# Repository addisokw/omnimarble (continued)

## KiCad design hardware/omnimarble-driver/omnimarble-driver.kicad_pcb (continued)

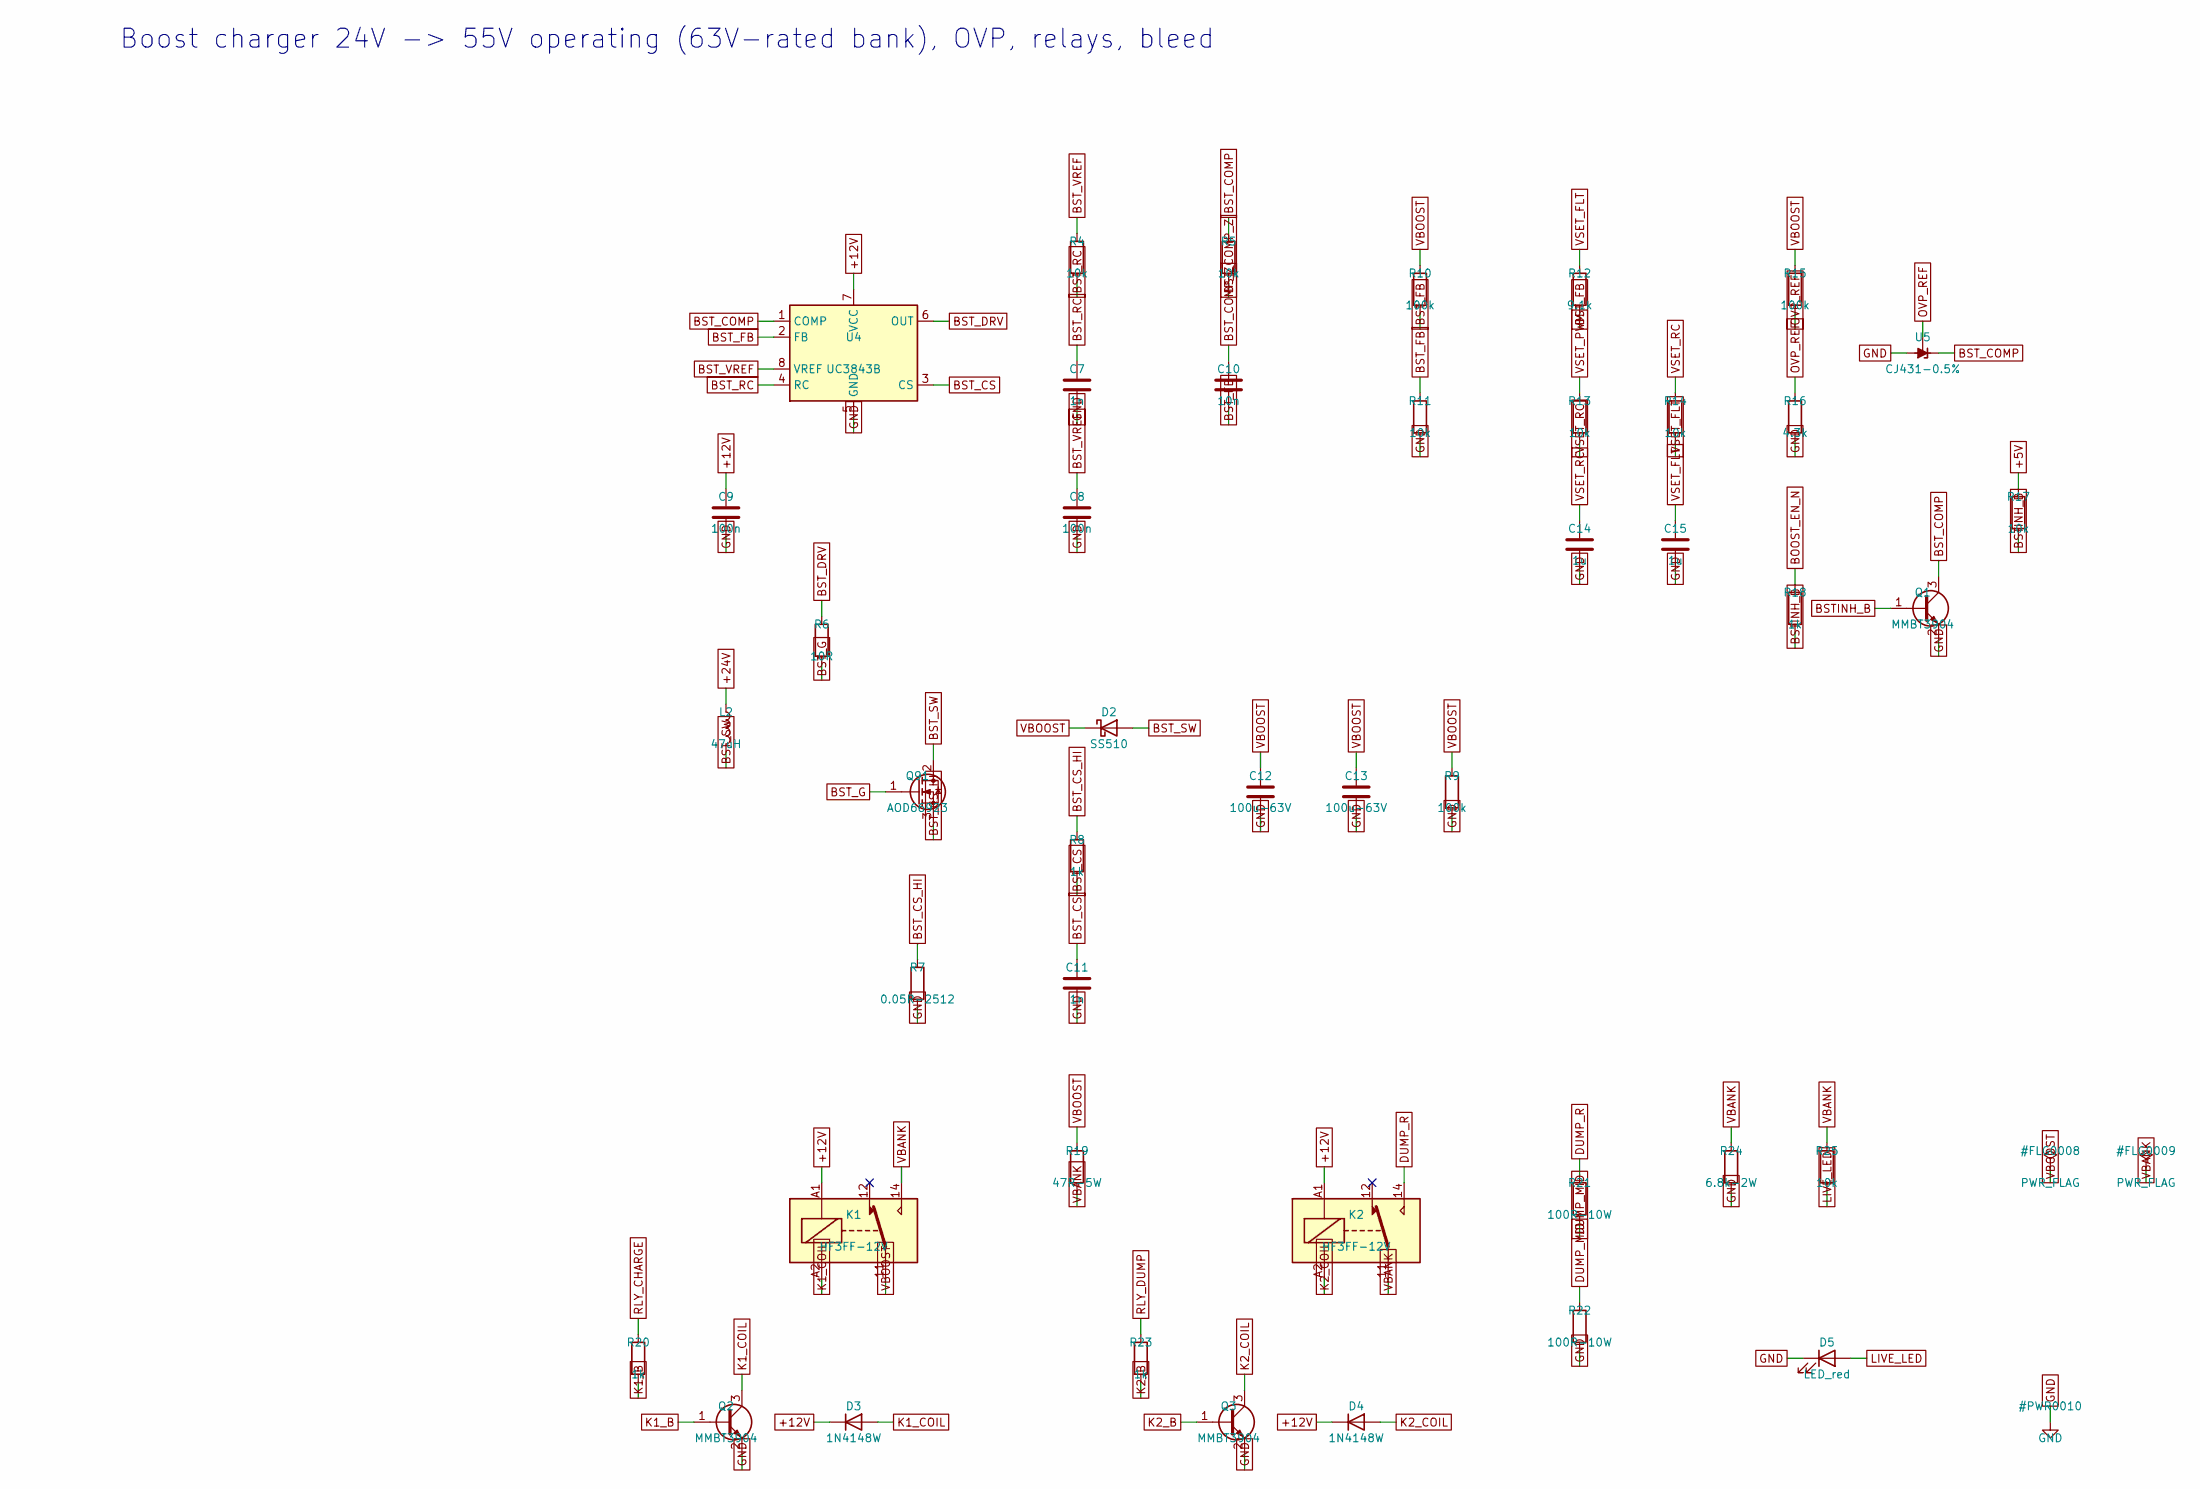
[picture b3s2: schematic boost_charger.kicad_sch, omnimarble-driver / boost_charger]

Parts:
C7, C11: 1n; C_0603_1608Metric; LCSC C1588
C8, C9: 100n; C_0603_1608Metric; LCSC C14663
C10: 10n; C_0603_1608Metric; LCSC C57112
C12, C13: 100u-63V; CP_Elec_10x10.5; LCSC C28241
C14, C15: 1u; C_0603_1608Metric; LCSC C15849
D2: SS510; D_SMA; LCSC C65010
D3, D4: 1N4148W; D_SOD-123; LCSC C81598
D5: LED_red; LED_0603_1608Metric; LCSC C2286
K1, K2: HF3FF-12V; Relay_HF3FF_T73; LCSC C399561
L2: 47uH; L_12x12mm_H8mm; LCSC C497913
Q1, Q2, Q3: MMBT3904; SOT-23; LCSC C20526
Q91: AOD66923; TO-252-2; LCSC C485687
R4, R5, R11, R13, R14, R17, R25: 10k; R_0603_1608Metric; LCSC C25804
R6: 10R; R_0603_1608Metric; LCSC C22859
R7: 0.05R-2512; R_2512_6332Metric; LCSC C2994645
R8, R18, R20, R23: 1k; R_0603_1608Metric; LCSC C21190
R9, R10, R15: 100k; R_0603_1608Metric; LCSC C25803
R12: 9.1k; R_0603_1608Metric; LCSC C23260
R16: 4.3k; R_0603_1608Metric; LCSC C23159
R19: 47R-5W; R_Box_L26.0mm_W5.0mm_P20.00mm; LCSC C5807995
R21, R22: 100R-10W; R_Radial_Power_L11.0mm_W7.0mm_P5.00mm; LCSC C216413
R24: 6.8k-2W; R_2512_6332Metric; LCSC ORDER-REVIEW
U4: UC3843B; SOIC-8_3.9x4.9mm_P1.27mm; LCSC C16414
U5: CJ431-0.5%; SOT-23; LCSC C3113

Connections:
+5V: R17.1; also elsewhere on the board
+12V: C9.1, D3.1 (K), D4.1 (K), K1.A1, K2.A1, U4.7 (VCC); also elsewhere on the board
+24V: L2.1; also elsewhere on the board
BOOST_EN_N: R18.1; also elsewhere on the board
BSTINH_B: Q1.1 (B), R17.2, R18.2
BST_COMP: Q1.3 (C), R5.1, U4.1 (COMP), U5.1 (K)
BST_COMP_Z: C10.1, R5.2
BST_CS: C11.1, R8.2, U4.3 (CS)
BST_CS_HI: Q91.3 (S), R7.1, R8.1
BST_DRV: R6.1, U4.6 (OUT)
BST_FB: C10.2, R10.2, R11.1, R12.2, U4.2 (FB)
BST_G: Q91.1 (G), R6.2
BST_RC: C7.1, R4.2, U4.4 (RC)
BST_SW: D2.2 (A), L2.2, Q91.2 (D)
BST_VREF: C8.1, R4.1, U4.8 (VREF)
DUMP_MID: R21.2, R22.1
DUMP_R: K2.14, R21.1
GND: C7.2, C8.2, C9.2, C11.2, C12.2, C13.2, C14.2, C15.2, D5.1 (K), Q1.2 (E), Q2.2 (E), Q3.2 (E), R7.2, R9.2, R11.2, R16.2, R22.2, R24.2, U4.5 (GND), U5.3 (A); also elsewhere on the board
K1_B: Q2.1 (B), R20.2
K1_COIL: D3.2 (A), K1.A2, Q2.3 (C)
K2_B: Q3.1 (B), R23.2
K2_COIL: D4.2 (A), K2.A2, Q3.3 (C)
LIVE_LED: D5.2 (A), R25.2
OVP_REF: R15.2, R16.1, U5.2 (REF)
RLY_CHARGE: R20.1; also elsewhere on the board
RLY_DUMP: R23.1; also elsewhere on the board
VBANK: K1.14, K2.11, R19.2, R24.1, R25.1; also elsewhere on the board
VBOOST: C12.1, C13.1, D2.1 (K), K1.11, R9.1, R10.1, R15.1, R19.1
VSET_FLT: C15.1, R12.1, R14.2
VSET_PWM: R13.1; also elsewhere on the board
VSET_RC: C14.1, R13.2, R14.1

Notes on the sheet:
Boost charger 24V -> 55V operating (63V-rated bank), OVP, relays, bleed

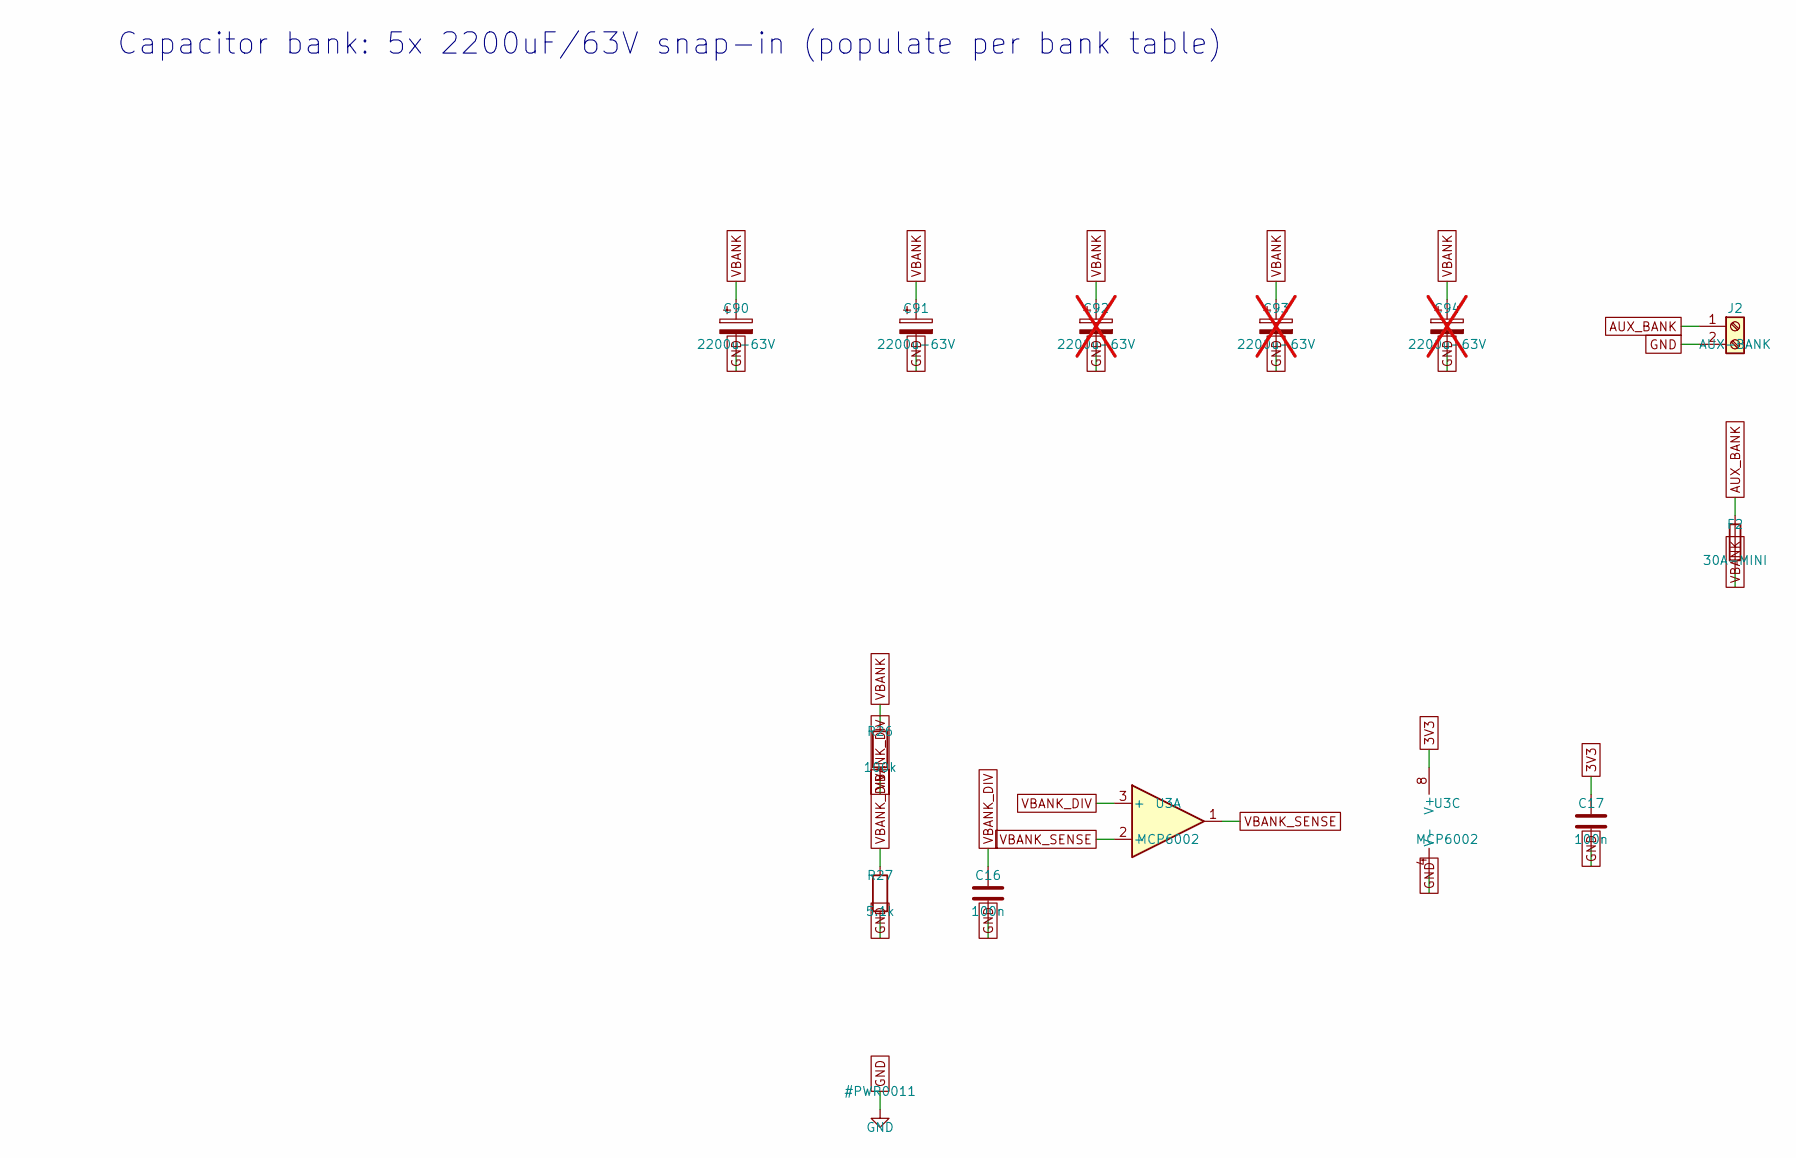
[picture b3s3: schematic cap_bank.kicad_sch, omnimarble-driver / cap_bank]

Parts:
C16, C17: 100n; C_0603_1608Metric; LCSC C14663
C90, C91: 2200u-63V; CP_Radial_D30.0mm_P10.00mm_SnapIn; LCSC C3724971
C92, C93, C94: 2200u-63V; CP_Radial_D30.0mm_P10.00mm_SnapIn; LCSC C3724971; not fitted
F2: 30A-MINI; Fuseholder_Blade_Mini_Keystone_3568; LCSC C5249699
J2: AUX-BANK; TerminalBarrier_1x02_P9.50mm; LCSC C60785
R26: 100k; R_0603_1608Metric; LCSC C25803
R27: 5.1k; R_0603_1608Metric; LCSC C23186
U3: MCP6002; SOIC-8_3.9x4.9mm_P1.27mm; LCSC C7377

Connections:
3V3: C17.1, U3.8 (V+); also elsewhere on the board
AUX_BANK: F2.1, J2.1
GND: C16.2, C17.2, C90.2, C91.2, C92.2, C93.2, C94.2, J2.2, R27.2, U3.4 (V-); also elsewhere on the board
VBANK: C90.1, C91.1, C92.1, C93.1, C94.1, F2.2, R26.1; also elsewhere on the board
VBANK_DIV: C16.1, R26.2, R27.1, U3.3 (+)
VBANK_SENSE: U3.1, U3.2 (-); also elsewhere on the board

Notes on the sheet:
Capacitor bank: 5x 2200uF/63V snap-in (populate per bank table)

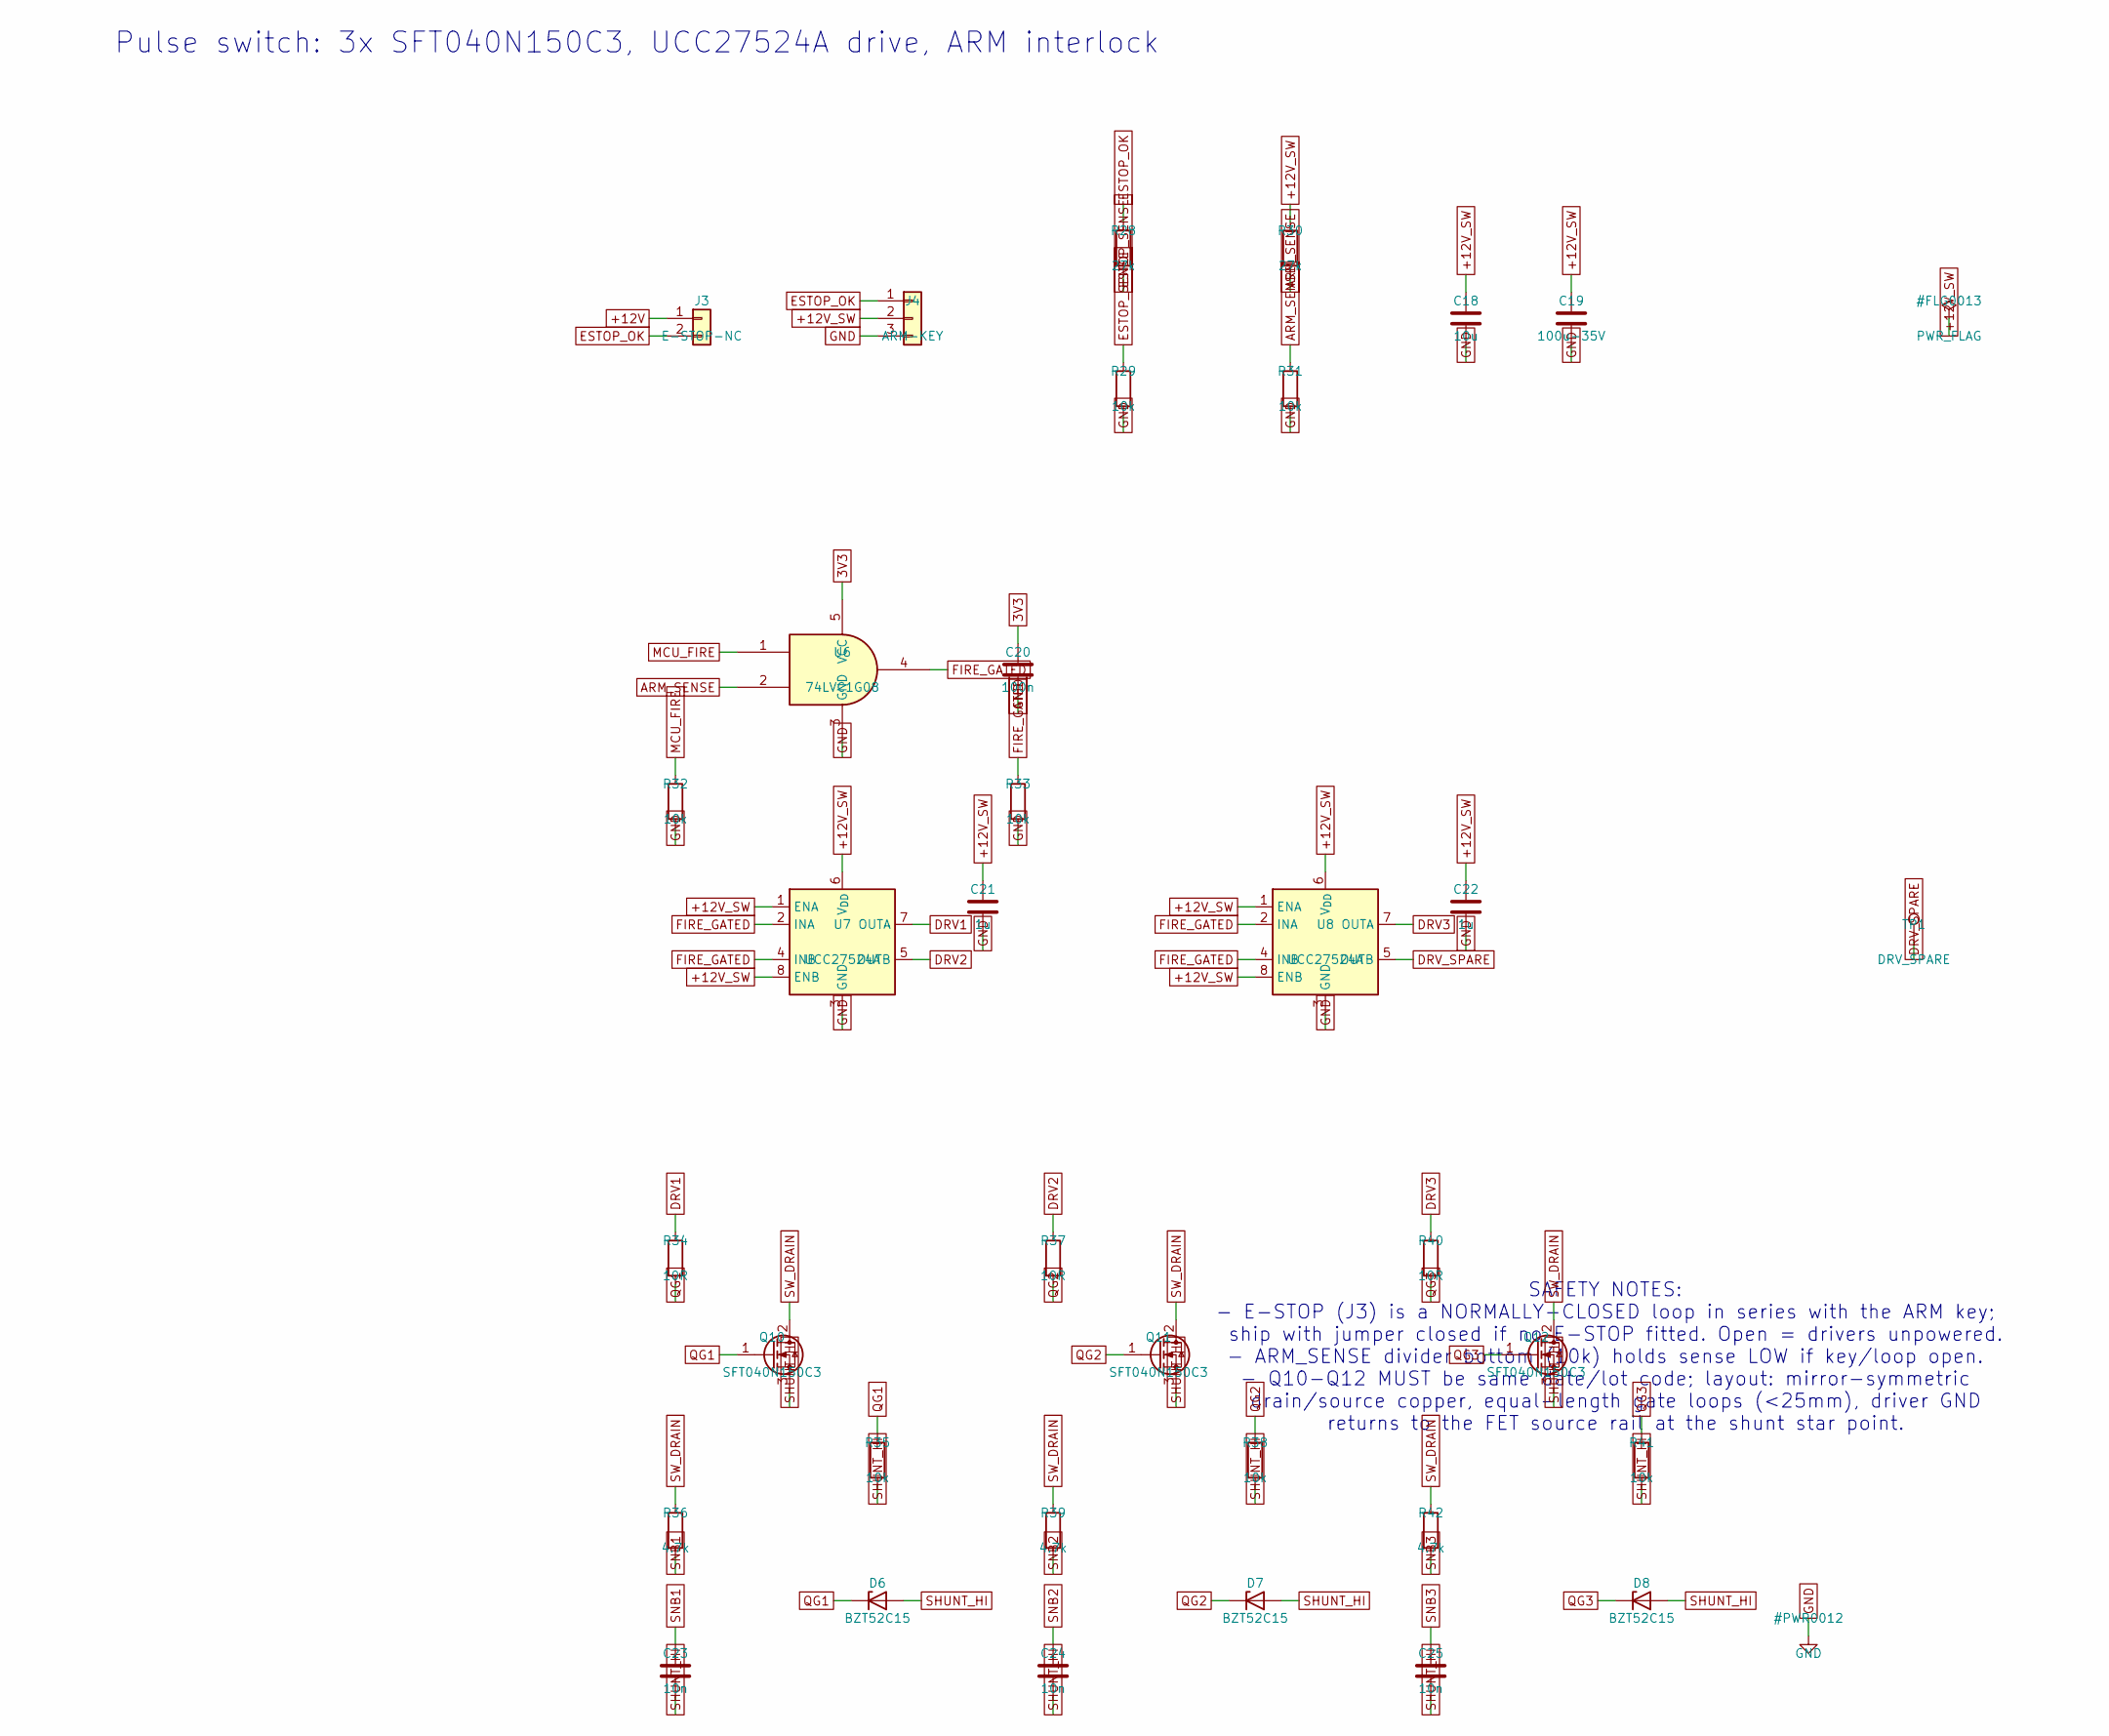
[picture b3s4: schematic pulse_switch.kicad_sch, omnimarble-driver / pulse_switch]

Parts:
C18: 10u; C_0805_2012Metric; LCSC C15850
C19: 100u-35V; CP_Elec_6.3x7.7; LCSC C176666
C20: 100n; C_0603_1608Metric; LCSC C14663
C21, C22: 1u; C_0603_1608Metric; LCSC C15849
C23, C24, C25: 10n; C_0603_1608Metric; LCSC C57112
D6, D7, D8: BZT52C15; D_SOD-123; LCSC C19077412
J3: E-STOP-NC; PinHeader_1x02_P2.54mm_Vertical
J4: ARM-KEY; PinHeader_1x03_P2.54mm_Vertical
Q10, Q11, Q12: SFT040N150C3; TOLL-8; LCSC C42395334
R28, R30: 27k; R_0603_1608Metric; LCSC C22967
R29, R31, R32, R33, R35, R38, R41: 10k; R_0603_1608Metric; LCSC C25804
R34, R37, R40: 10R; R_0603_1608Metric; LCSC C22859
R36, R39, R42: 4.7k; R_2512_6332Metric; LCSC C23162
TP1: DRV_SPARE; TestPoint_Pad_1.5x1.5mm
U6: 74LVC1G08; SOT-353_SC-70-5; LCSC C7832
U7, U8: UCC27524A; SOIC-8_3.9x4.9mm_P1.27mm; LCSC C185857

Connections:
3V3: C20.1, U6.5 (VCC); also elsewhere on the board
+12V: J3.1; also elsewhere on the board
+12V_SW: C18.1, C19.1, C21.1, C22.1, J4.2, R30.1, U7.1 (ENA), U7.6 (V_{DD}), U7.8 (ENB), U8.1 (ENA), U8.6 (V_{DD}), U8.8 (ENB)
ARM_SENSE: R30.2, R31.1, U6.2; also elsewhere on the board
DRV1: R34.1, U7.7 (OUTA)
DRV2: R37.1, U7.5 (OUTB)
DRV3: R40.1, U8.7 (OUTA)
DRV_SPARE: TP1.1, U8.5 (OUTB)
ESTOP_OK: J3.2, J4.1, R28.1
ESTOP_SENSE: R28.2, R29.1; also elsewhere on the board
FIRE_GATED: R33.1, U6.4, U7.2 (INA), U7.4 (INB), U8.2 (INA), U8.4 (INB)
GND: C18.2, C19.2, C20.2, C21.2, C22.2, J4.3, R29.2, R31.2, R32.2, R33.2, U6.3 (GND), U7.3 (GND), U8.3 (GND); also elsewhere on the board
MCU_FIRE: R32.1, U6.1; also elsewhere on the board
QG1: D6.1 (K), Q10.1 (G), R34.2, R35.1
QG2: D7.1 (K), Q11.1 (G), R37.2, R38.1
QG3: D8.1 (K), Q12.1 (G), R40.2, R41.1
SHUNT_HI: C23.2, C24.2, C25.2, D6.2 (A), D7.2 (A), D8.2 (A), Q10.3 (S), Q11.3 (S), Q12.3 (S), R35.2, R38.2, R41.2; also elsewhere on the board
SNB1: C23.1, R36.2
SNB2: C24.1, R39.2
SNB3: C25.1, R42.2
SW_DRAIN: Q10.2 (D), Q11.2 (D), Q12.2 (D), R36.1, R39.1, R42.1; also elsewhere on the board

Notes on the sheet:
Pulse switch: 3x SFT040N150C3, UCC27524A drive, ARM interlock
SAFETY NOTES: - E-STOP (J3) is a NORMALLY-CLOSED loop in series with the ARM key; ship with jumper closed if no E-STOP fitted. Open = drivers unpowered. - ARM_SENSE divider bottom (10k) holds sense LOW if key/loop open. - Q10-Q12 MUST be same date/lot code; layout: mirror-symmetric drain/source cop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

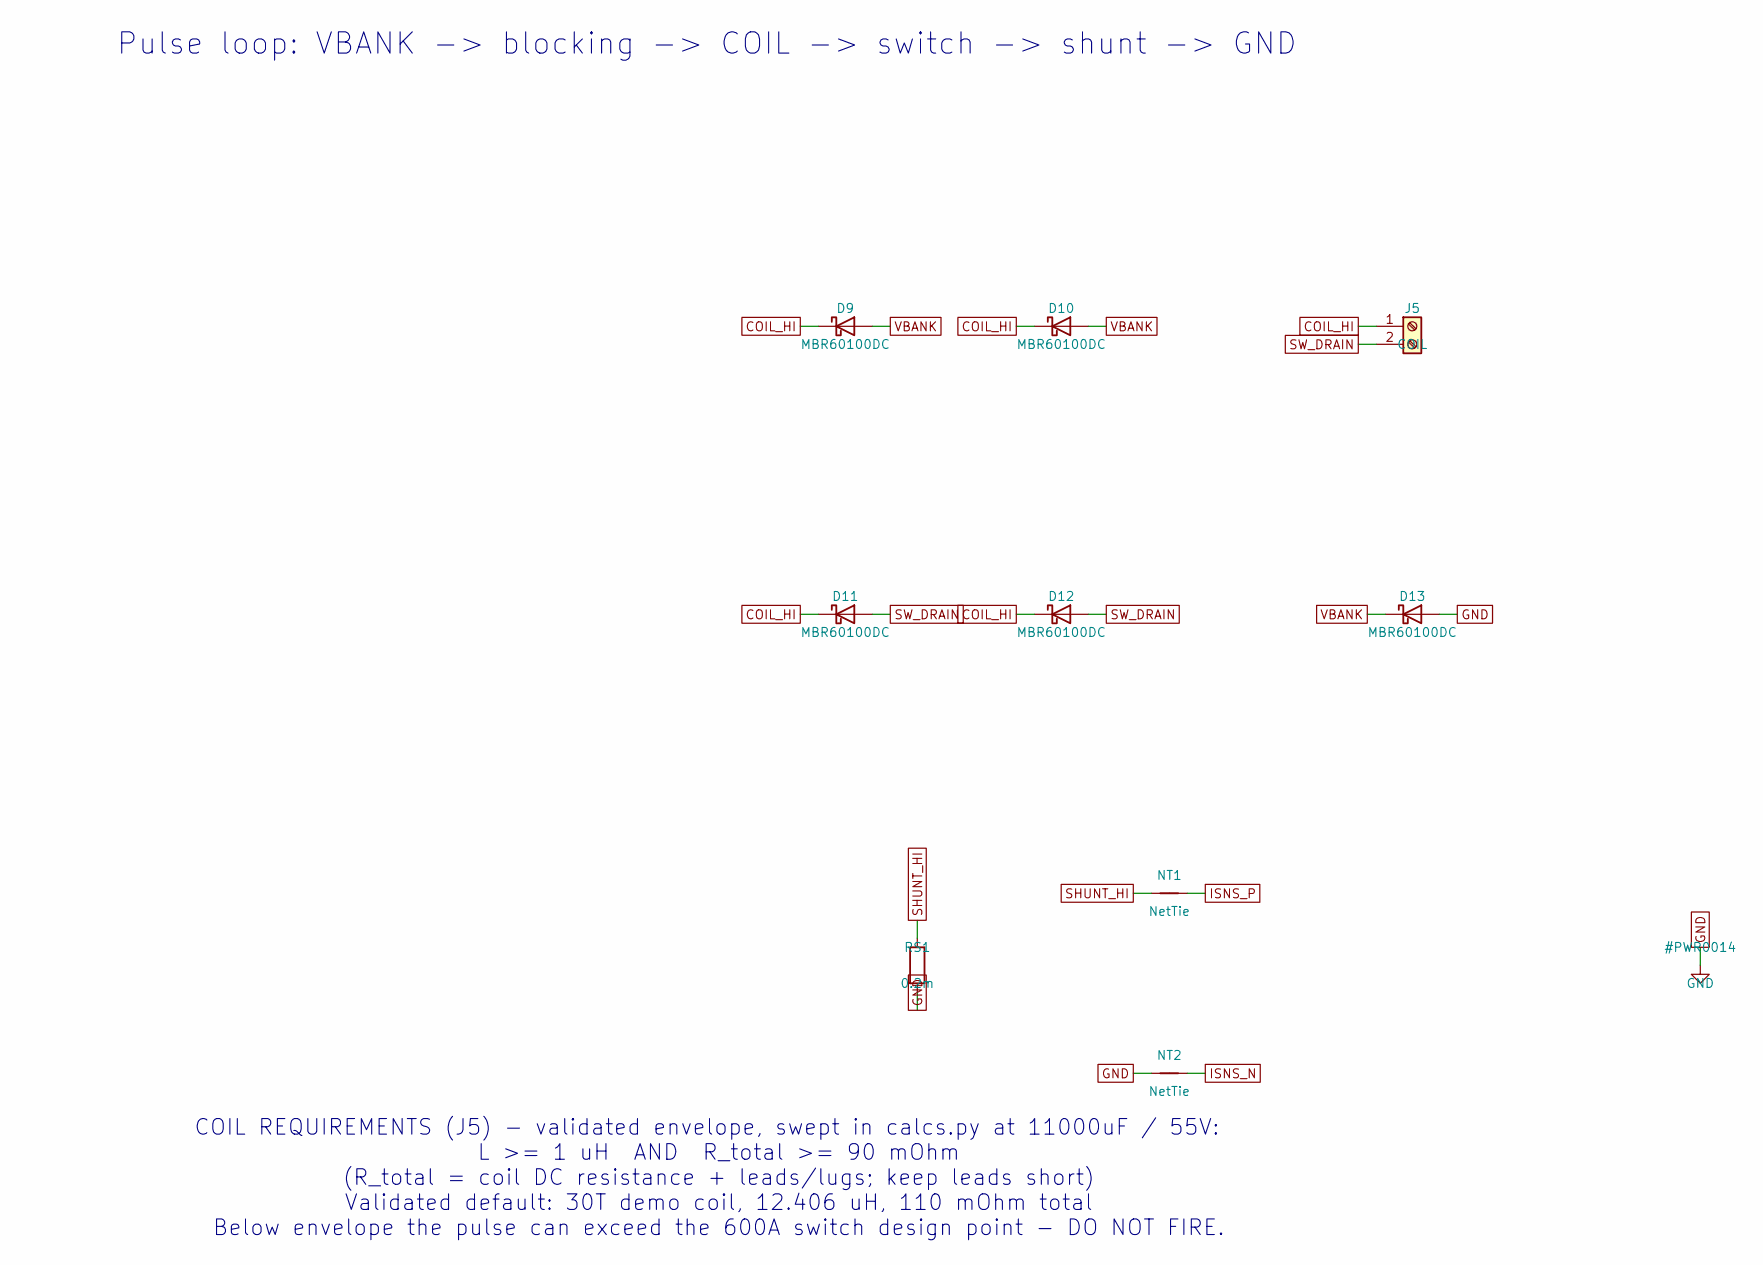
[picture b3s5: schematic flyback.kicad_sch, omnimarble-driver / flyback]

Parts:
D9, D10, D11, D12, D13: MBR60100DC; D2PAK_MBR60100DC; LCSC C6069541
J5: COIL; TerminalBarrier_1x02_P9.50mm; LCSC C60785
NT1, NT2: NetTie; NetTie-2_SMD_Pad0.5mm
RS1: 0.2m; Shunt_5930; LCSC C469442

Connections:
COIL_HI: D9.1 (K), D10.1 (K), D11.1 (K), D12.1 (K), J5.1
GND: D13.2 (A), NT2.1, RS1.2; also elsewhere on the board
ISNS_N: NT2.2; also elsewhere on the board
ISNS_P: NT1.2; also elsewhere on the board
SHUNT_HI: NT1.1, RS1.1; also elsewhere on the board
SW_DRAIN: D11.2 (A), D12.2 (A), J5.2; also elsewhere on the board
VBANK: D9.2 (A), D10.2 (A), D13.1 (K); also elsewhere on the board

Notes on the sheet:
Pulse loop: VBANK -> blocking -> COIL -> switch -> shunt -> GND
COIL REQUIREMENTS (J5) - validated envelope, swept in calcs.py at 11000uF / 55V: L >= 1 uH AND R_total >= 90 mOhm (R_total = coil DC resistance + leads/lugs; keep leads short) Validated default: 30T demo coil, 12.406 uH, 110 mOhm total Below envelope the pulse can exceed the 600A switch design poin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

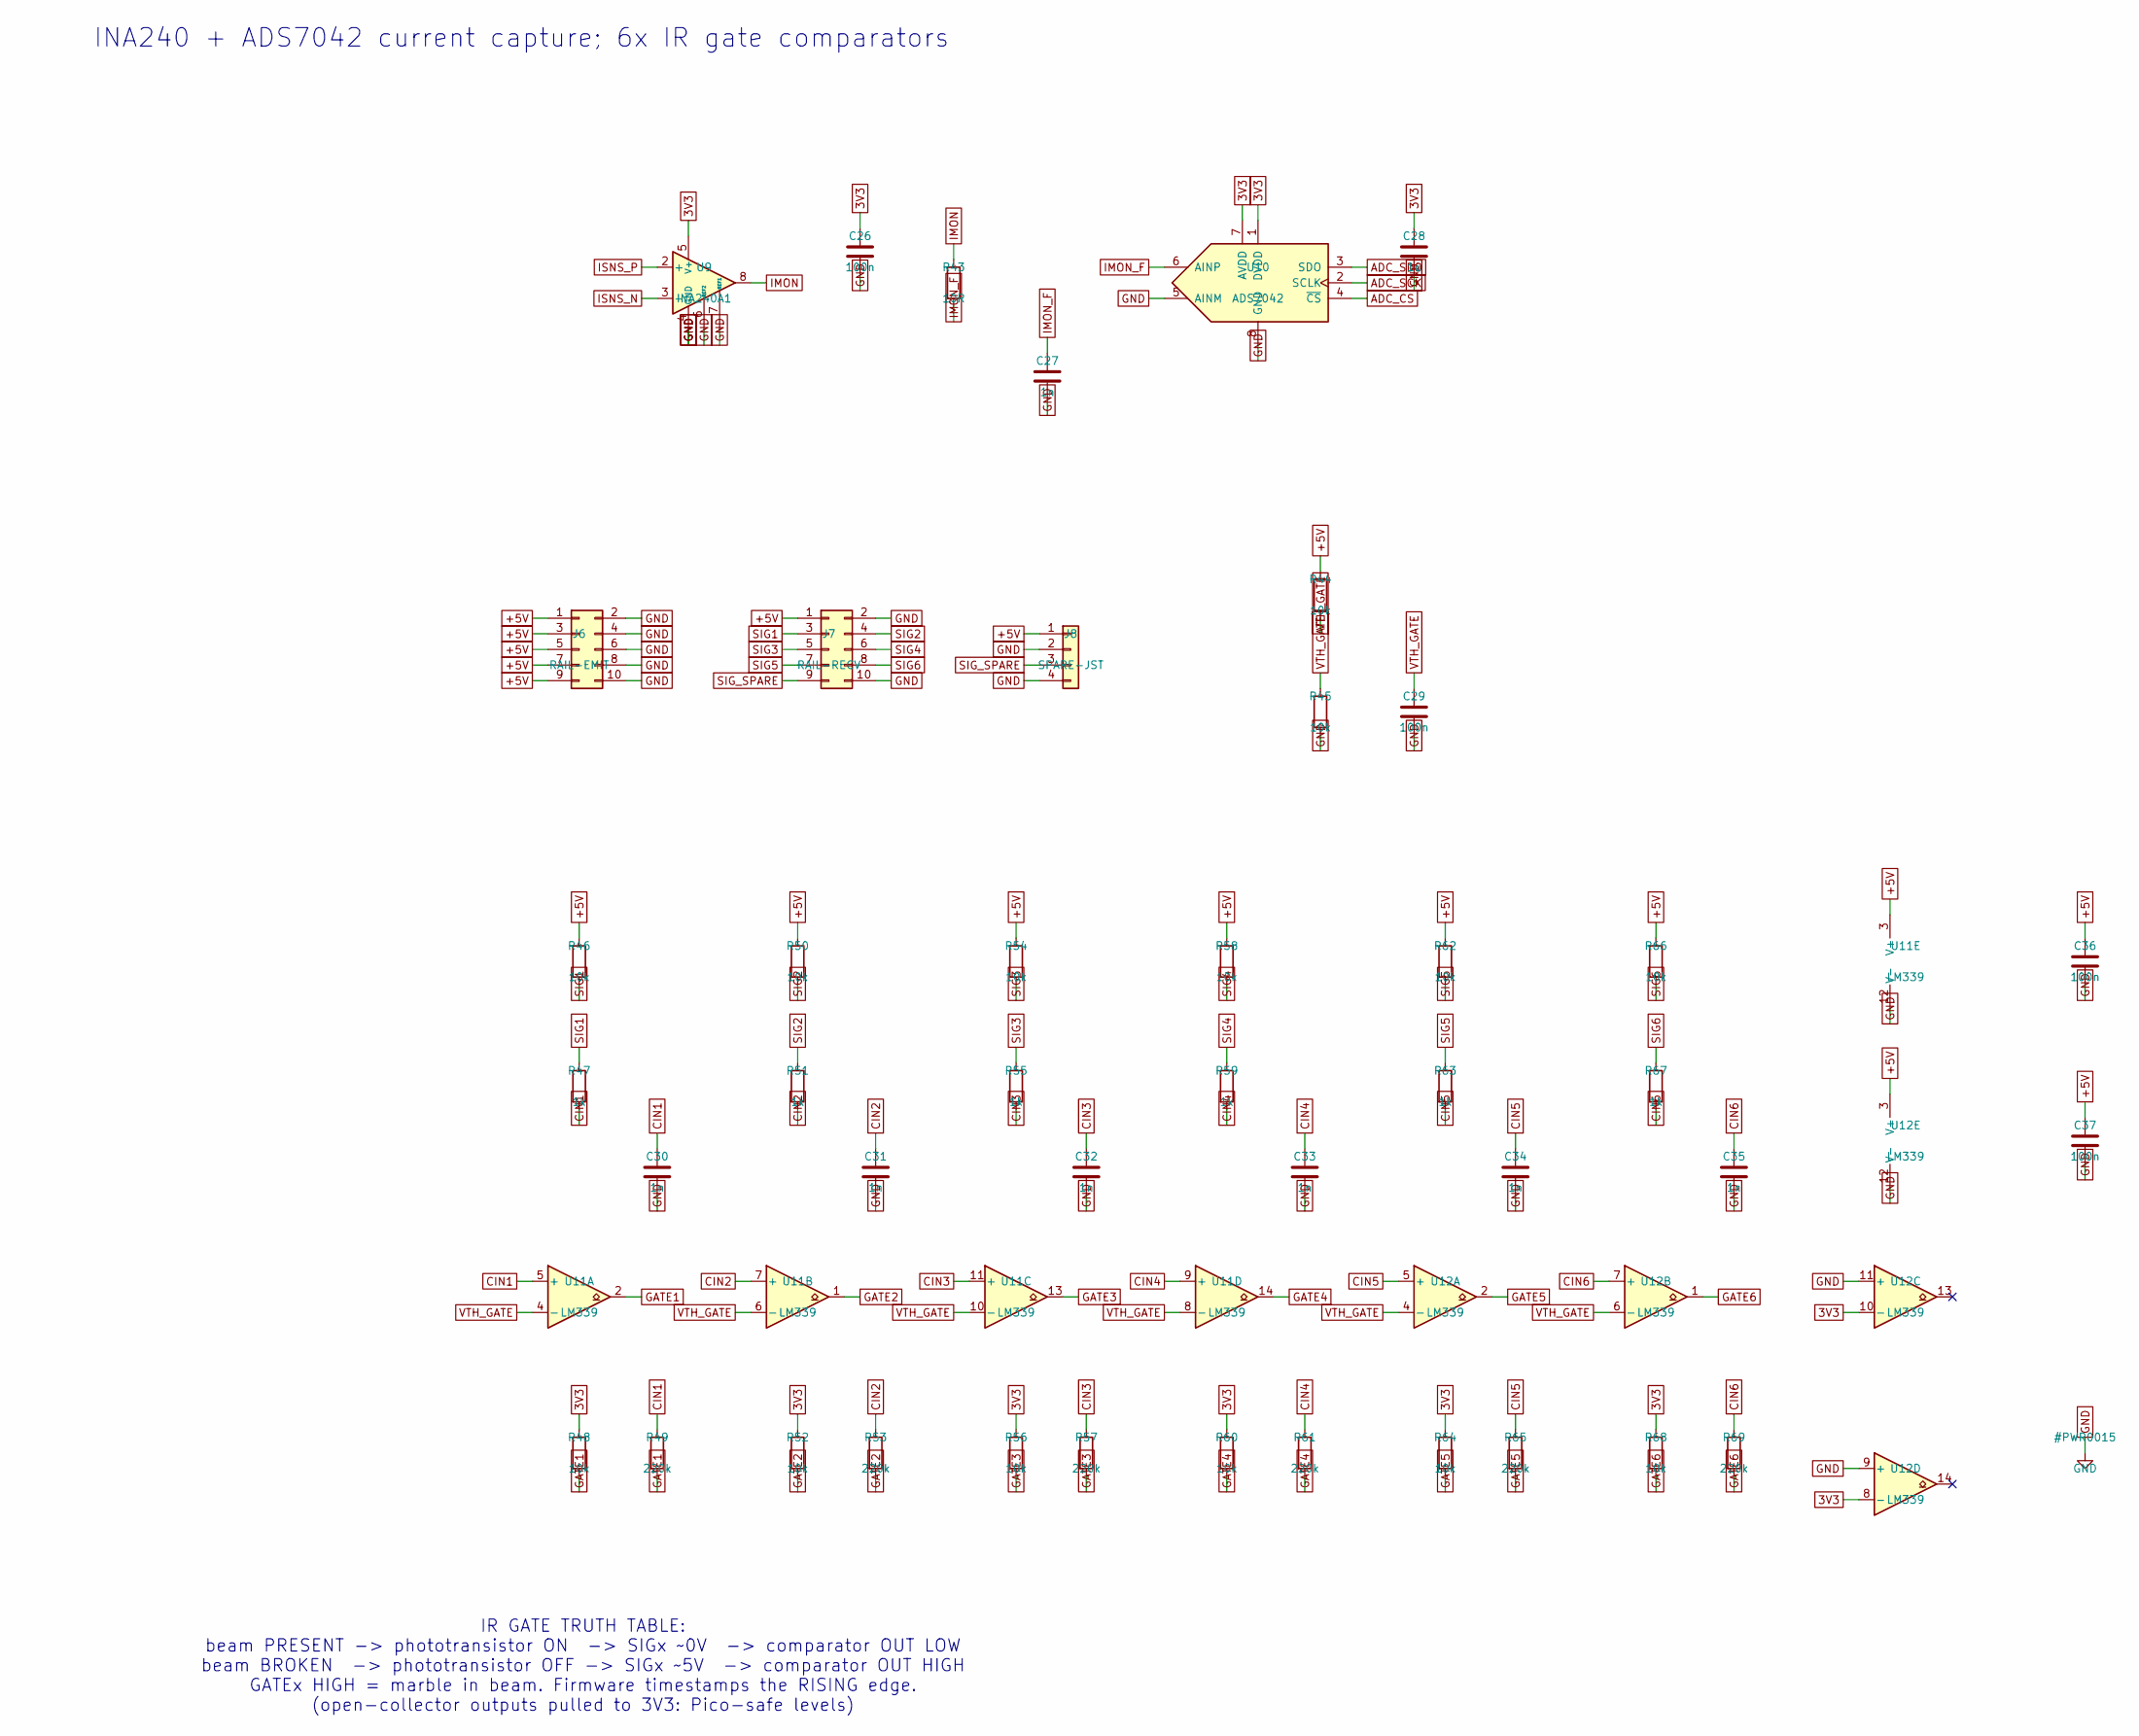
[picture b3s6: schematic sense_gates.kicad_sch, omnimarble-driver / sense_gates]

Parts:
C26, C29, C36, C37: 100n; C_0603_1608Metric; LCSC C14663
C27, C30, C31, C32, C33, C34, C35: 1n; C_0603_1608Metric; LCSC C1588
C28: 1u; C_0603_1608Metric; LCSC C15849
J6: RAIL-EMIT; IDC-Header_2x05_P2.54mm_Vertical; LCSC C5665
J7: RAIL-RECV; IDC-Header_2x05_P2.54mm_Vertical; LCSC C5665
J8: SPARE-JST; JST_XH_B4B-XH-A_1x04_P2.50mm_Vertical; LCSC C144395
R43: 10R; R_0603_1608Metric; LCSC C22859
R44, R45, R46, R48, R50, R52, R54, R56, R58, R60, R62, R64, R66, R68: 10k; R_0603_1608Metric; LCSC C25804
R47, R51, R55, R59, R63, R67: 1k; R_0603_1608Metric; LCSC C21190
R49, R53, R57, R61, R65, R69: 220k; R_0603_1608Metric; LCSC C22961
U9: INA240A1; TSSOP-8_3x3mm_P0.65mm; LCSC C93965
U10: ADS7042; VSSOP-8_2.3x2mm_P0.5mm; LCSC C701641
U11, U12: LM339; SOIC-14_3.9x8.7mm_P1.27mm; LCSC C7948

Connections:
3V3: C26.1, C28.1, R48.1, R52.1, R56.1, R60.1, R64.1, R68.1, U9.5 (V+), U10.1 (DVDD), U10.7 (AVDD), U12.8 (-), U12.10 (-); also elsewhere on the board
+5V: C36.1, C37.1, J6.1, J6.3, J6.5, J6.7, J6.9, J7.1, J8.1, R44.1, R46.1, R50.1, R54.1, R58.1, R62.1, R66.1, U11.3 (V+), U12.3 (V+); also elsewhere on the board
ADC_CS: U10.4 (~CS); also elsewhere on the board
ADC_SCK: U10.2 (SCLK); also elsewhere on the board
ADC_SDO: U10.3 (SDO); also elsewhere on the board
CIN1: C30.1, R47.2, R49.1, U11.5 (+)
CIN2: C31.1, R51.2, R53.1, U11.7 (+)
CIN3: C32.1, R55.2, R57.1, U11.11 (+)
CIN4: C33.1, R59.2, R61.1, U11.9 (+)
CIN5: C34.1, R63.2, R65.1, U12.5 (+)
CIN6: C35.1, R67.2, R69.1, U12.7 (+)
GATE1: R48.2, R49.2, U11.2; also elsewhere on the board
GATE2: R52.2, R53.2, U11.1; also elsewhere on the board
GATE3: R56.2, R57.2, U11.13; also elsewhere on the board
GATE4: R60.2, R61.2, U11.14; also elsewhere on the board
GATE5: R64.2, R65.2, U12.2; also elsewhere on the board
GATE6: R68.2, R69.2, U12.1; also elsewhere on the board
GND: C26.2, C27.2, C28.2, C29.2, C30.2, C31.2, C32.2, C33.2, C34.2, C35.2, C36.2, C37.2, J6.2, J6.4, J6.6, J6.8, J6.10, J7.2, J7.10, J8.2, J8.4, R45.2, U9.1 (GND), U9.4 (GND), U9.6 (REF2), U9.7 (REF1), U10.5 (AINM), U10.8 (GND), U11.12 (V-), U12.9 (+), U12.11 (+), U12.12 (V-); also elsewhere on the board
IMON: R43.1, U9.8
IMON_F: C27.1, R43.2, U10.6 (AINP)
ISNS_N: U9.3 (-); also elsewhere on the board
ISNS_P: U9.2 (+); also elsewhere on the board
SIG1: J7.3, R46.2, R47.1
SIG2: J7.4, R50.2, R51.1
SIG3: J7.5, R54.2, R55.1
SIG4: J7.6, R58.2, R59.1
SIG5: J7.7, R62.2, R63.1
SIG6: J7.8, R66.2, R67.1
SIG_SPARE: J7.9, J8.3
VTH_GATE: C29.1, R44.2, R45.1, U11.4 (-), U11.6 (-), U11.8 (-), U11.10 (-), U12.4 (-), U12.6 (-)

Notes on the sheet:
INA240 + ADS7042 current capture; 6x IR gate comparators
IR GATE TRUTH TABLE: beam PRESENT -> phototransistor ON -> SIGx ~0V -> comparator OUT LOW beam BROKEN -> phototransistor OFF -> SIGx ~5V -> comparator OUT HIGH GATEx HIGH = marble in beam. Firmware timestamps the RISING edge. (open-collector outputs pulled to 3V3: Pico-safe levels)
